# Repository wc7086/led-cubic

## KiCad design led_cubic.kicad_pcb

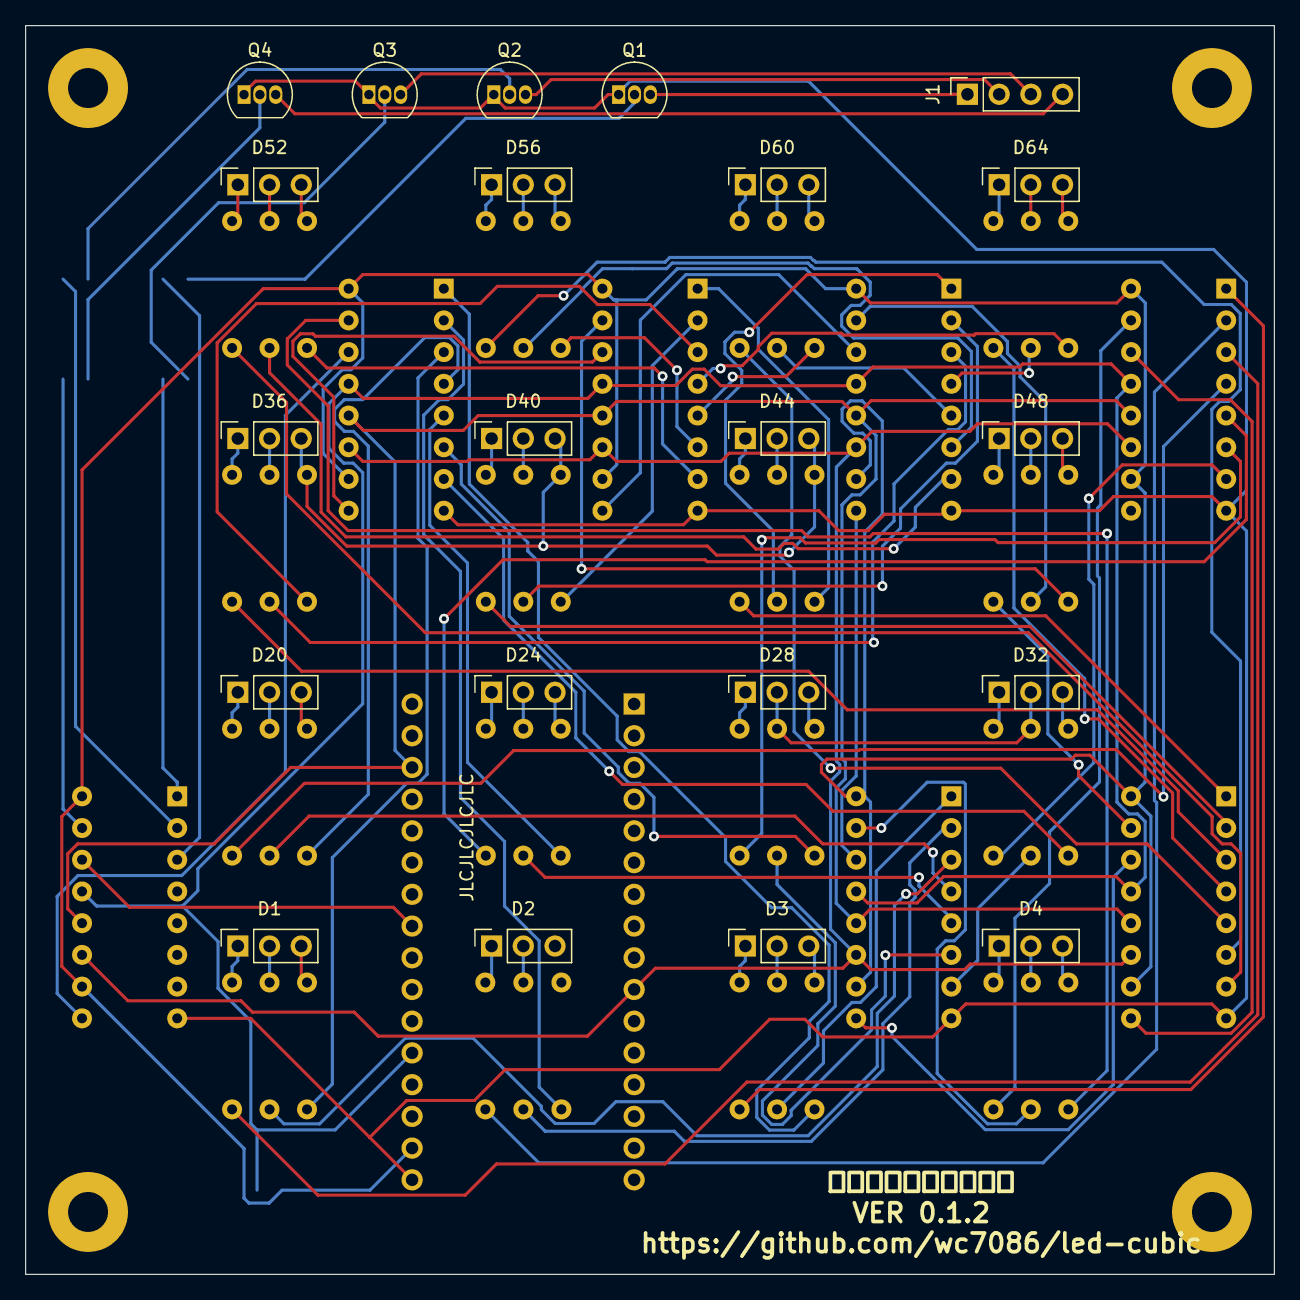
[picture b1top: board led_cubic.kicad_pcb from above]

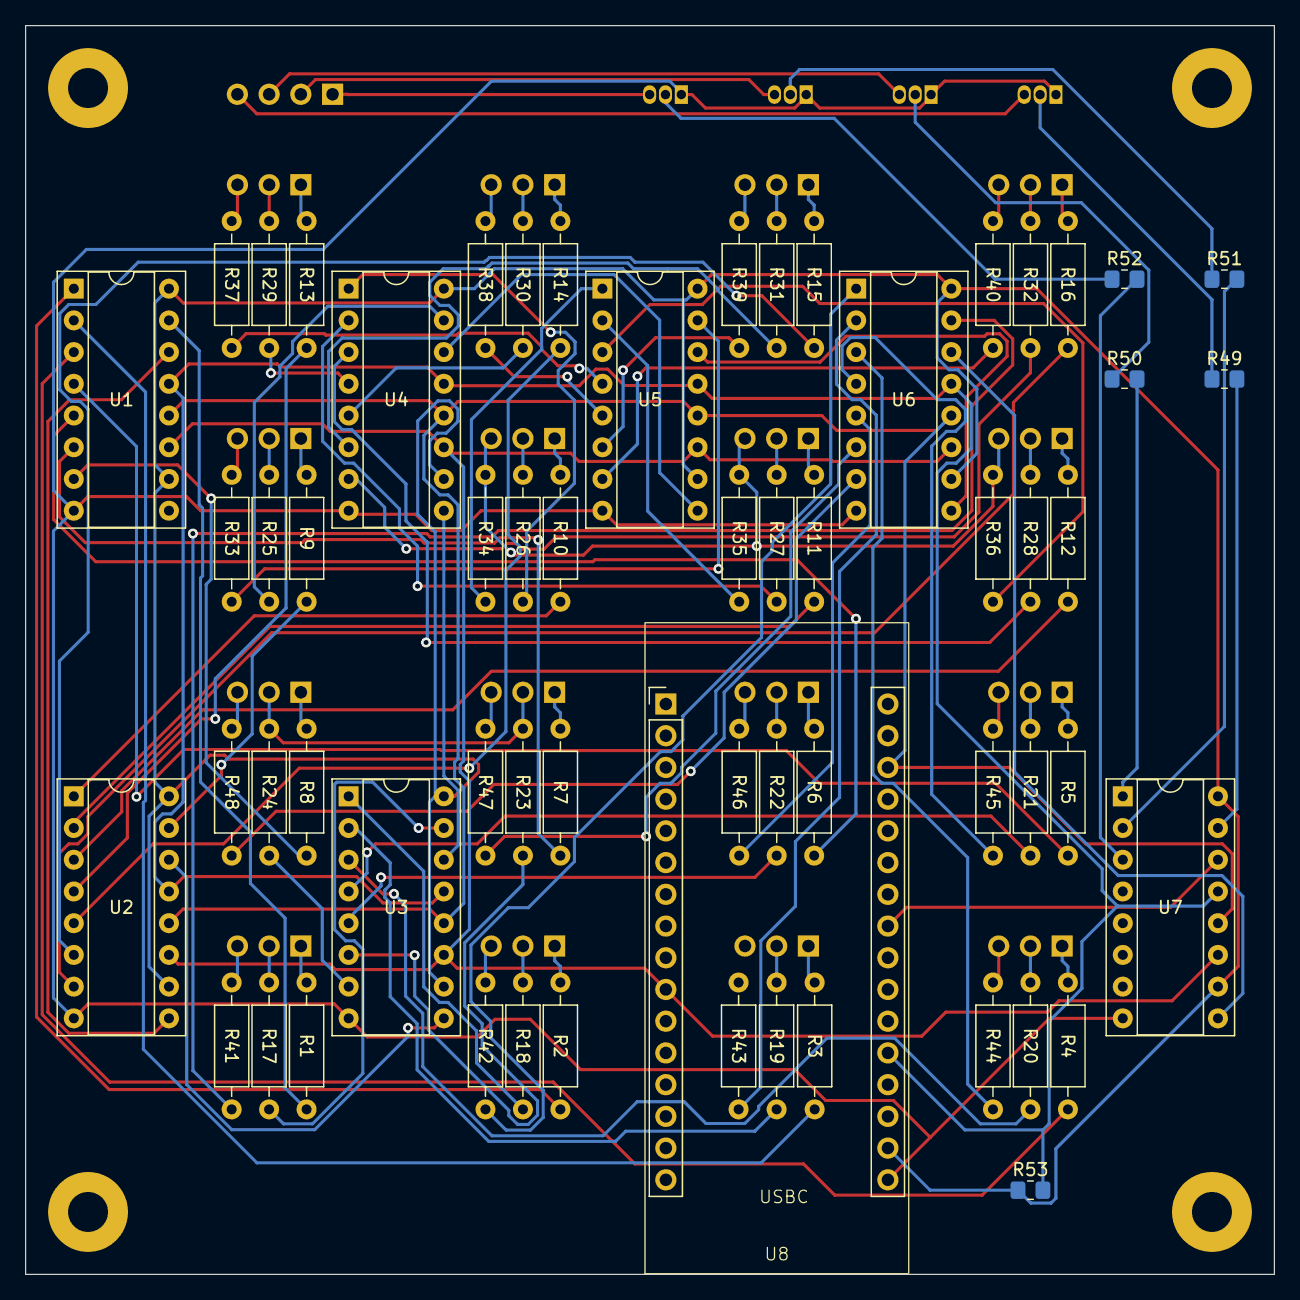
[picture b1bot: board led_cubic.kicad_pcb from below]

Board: 2 copper layers, 100.0 x 100.0 mm, 86 parts (61 on the bottom side), 84 nets.

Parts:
D1, D2, D3, D4, D20, D24, D28, D32, D36, D40, D44, D48, D52, D56, D60, D64: LED_BGKR; PinSocket_1x03_P2.54mm_Vertical
J1: Cathode Layer; PinSocket_1x04_P2.54mm_Vertical
P1, P2, P3, P4: MountingHole_3.2mm_M3_Pad
Q1, Q2, Q3, Q4: 2N2222; TO-92_Inline
R1, R2, R3, R4, R5, R6, R7, R8, R9, R10, R11, R12, R13, R14, R15, R16, R17, R18, R19, R20, R21, R22, R23, R24, R25, R26, R27, R28, R29, R30, R31, R32, R33, R34, R35, R36, R37, R38, R39, R40, R41, R42, R43, R44, R45, R46, R47, R48: 330R; R_Axial_DIN0207_L6.3mm_D2.5mm_P10.16mm_Horizontal
R49, R50, R51, R52: 1k; R_0805_2012Metric_Pad1.20x1.40mm_HandSolder
R53: 10k; R_0805_2012Metric_Pad1.20x1.40mm_HandSolder
U1, U2, U3, U4, U5, U6, U7: 74HC595; DIP-16_W7.62mm_Socket
U8: CORE-ESP32-C3-DevKit; CORE-ESP32-C3-DevKit-THT

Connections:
+5V: R53.2, U1.10 (~SRCLR), U1.16 (VCC), U2.10 (~SRCLR), U2.16 (VCC), U3.10 (~SRCLR), U3.16 (VCC), U4.10 (~SRCLR), U4.16 (VCC), U5.10 (~SRCLR), U5.16 (VCC), U6.10 (~SRCLR), U6.16 (VCC), U7.10 (~SRCLR), U7.16 (VCC), U8.31 (5V)
/B1: D1.1 (BA), D2.1 (BA), D3.1 (BA), D4.1 (BA), R1.1, R2.1, R3.1, R4.1
/B2: D20.1 (BA), D24.1 (BA), D28.1 (BA), D32.1 (BA), R5.1, R6.1, R7.1, R8.1
/B3: D36.1 (BA), D40.1 (BA), D44.1 (BA), D48.1 (BA), R9.1, R10.1, R11.1, R12.1
/B4: D52.1 (BA), D56.1 (BA), D60.1 (BA), D64.1 (BA), R13.1, R14.1, R15.1, R16.1
/G1: D1.2 (GA), D2.2 (GA), D3.2 (GA), D4.2 (GA), R17.1, R18.1, R19.1, R20.1
/G2: D20.2 (GA), D24.2 (GA), D28.2 (GA), D32.2 (GA), R21.1, R22.1, R23.1, R24.1
/G3: D36.2 (GA), D40.2 (GA), D44.2 (GA), D48.2 (GA), R25.1, R26.1, R27.1, R28.1
/G4: D52.2 (GA), D56.2 (GA), D60.2 (GA), D64.2 (GA), R29.1, R30.1, R31.1, R32.1
/GND1: J1.1, Q1.3 (C)
/GND2: J1.2, Q2.3 (C)
/GND3: J1.3, Q3.3 (C)
/GND4: J1.4, Q4.3 (C)
/P9: U5.14 (SER), U6.9 (QH')
/P10: U1.11 (SRCLK), U2.11 (SRCLK), U3.11 (SRCLK), U4.11 (SRCLK), U5.11 (SRCLK), U6.11 (SRCLK), U7.11 (SRCLK), U8.10 (GPIO13)
/P19: U1.12 (RCLK), U2.12 (RCLK), U3.12 (RCLK), U4.12 (RCLK), U5.12 (RCLK), U6.12 (RCLK), U7.12 (RCLK), U8.19 (GPIO2/SPICK/PWM2)
/P24: U7.14 (SER), U8.24 (GPIO11)
/P28: R53.1, U1.13 (~OE), U2.13 (~OE), U3.13 (~OE), U4.13 (~OE), U5.13 (~OE), U6.13 (~OE), U7.13 (~OE), U8.28 (GPIO4/SDA/ADC4)
/R1: D1.4 (RA), D2.4 (RA), D3.4 (RA), D4.4 (RA), R41.1, R42.1, R43.1, R44.1
/R2: D20.4 (RA), D24.4 (RA), D28.4 (RA), D32.4 (RA), R45.1, R46.1, R47.1, R48.1
/R3: D36.4 (RA), D40.4 (RA), D44.4 (RA), D48.4 (RA), R33.1, R34.1, R35.1, R36.1
/R4: D52.4 (RA), D56.4 (RA), D60.4 (RA), D64.4 (RA), R37.1, R38.1, R39.1, R40.1
GND: Q1.1 (E), Q2.1 (E), Q3.1 (E), Q4.1 (E), U1.8 (GND), U2.8 (GND), U3.8 (GND), U4.8 (GND), U5.8 (GND), U6.8 (GND), U7.8 (GND), U8.32 (GND)
unnamed: Q1.2 (B), R52.1
unnamed: Q2.2 (B), R51.1
unnamed: Q3.2 (B), R50.1
unnamed: Q4.2 (B), R49.1
unnamed: R1.2, U1.15 (QA)
unnamed: R2.2, U1.1 (QB)
unnamed: R3.2, U1.2 (QC)
unnamed: R4.2, U1.3 (QD)
unnamed: R5.2, U1.4 (QE)
unnamed: R6.2, U1.5 (QF)
unnamed: R7.2, U1.6 (QG)
unnamed: R8.2, U1.7 (QH)
unnamed: U1.14 (SER), U2.9 (QH')
unnamed: R9.2, U2.15 (QA)
unnamed: R10.2, U2.1 (QB)
unnamed: R11.2, U2.2 (QC)
unnamed: R12.2, U2.3 (QD)
unnamed: R13.2, U2.4 (QE)
unnamed: R14.2, U2.5 (QF)
unnamed: R15.2, U2.6 (QG)
unnamed: R16.2, U2.7 (QH)
unnamed: U2.14 (SER), U3.9 (QH')
unnamed: R17.2, U3.15 (QA)
unnamed: R18.2, U3.1 (QB)
unnamed: R19.2, U3.2 (QC)
unnamed: R20.2, U3.3 (QD)
unnamed: R21.2, U3.4 (QE)
unnamed: R22.2, U3.5 (QF)
unnamed: R23.2, U3.6 (QG)
unnamed: R24.2, U3.7 (QH)
unnamed: U3.14 (SER), U4.9 (QH')
unnamed: R25.2, U4.15 (QA)
unnamed: R26.2, U4.1 (QB)
unnamed: R27.2, U4.2 (QC)
unnamed: R28.2, U4.3 (QD)
unnamed: R29.2, U4.4 (QE)
unnamed: R30.2, U4.5 (QF)
unnamed: R31.2, U4.6 (QG)
unnamed: R32.2, U4.7 (QH)
unnamed: U4.14 (SER), U5.9 (QH')
unnamed: R33.2, U5.15 (QA)
unnamed: R34.2, U5.1 (QB)
unnamed: R35.2, U5.2 (QC)
unnamed: R36.2, U5.3 (QD)
unnamed: R37.2, U5.4 (QE)
unnamed: R38.2, U5.5 (QF)
unnamed: R39.2, U5.6 (QG)
unnamed: R40.2, U5.7 (QH)
unnamed: R41.2, U6.15 (QA)
unnamed: R42.2, U6.1 (QB)
unnamed: R43.2, U6.2 (QC)
unnamed: R44.2, U6.3 (QD)
unnamed: R45.2, U6.4 (QE)
unnamed: R46.2, U6.5 (QF)
unnamed: R47.2, U6.6 (QG)
unnamed: R48.2, U6.7 (QH)
unnamed: U6.14 (SER), U7.9 (QH')
unnamed: R49.2, U7.15 (QA)
unnamed: R50.2, U7.1 (QB)
unnamed: R51.2, U7.2 (QC)
unnamed: R52.2, U7.3 (QD)

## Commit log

2023-05-30 0.1.0
2023-05-30 0.1.1
    修改布局和PCB大小并添加M3螺丝孔
2023-05-30 0.1.2
    调整 LED 插座焊盘间距，修改布局，重新布线
2023-06-03 修复PCB，删除每排LED的并联线路
